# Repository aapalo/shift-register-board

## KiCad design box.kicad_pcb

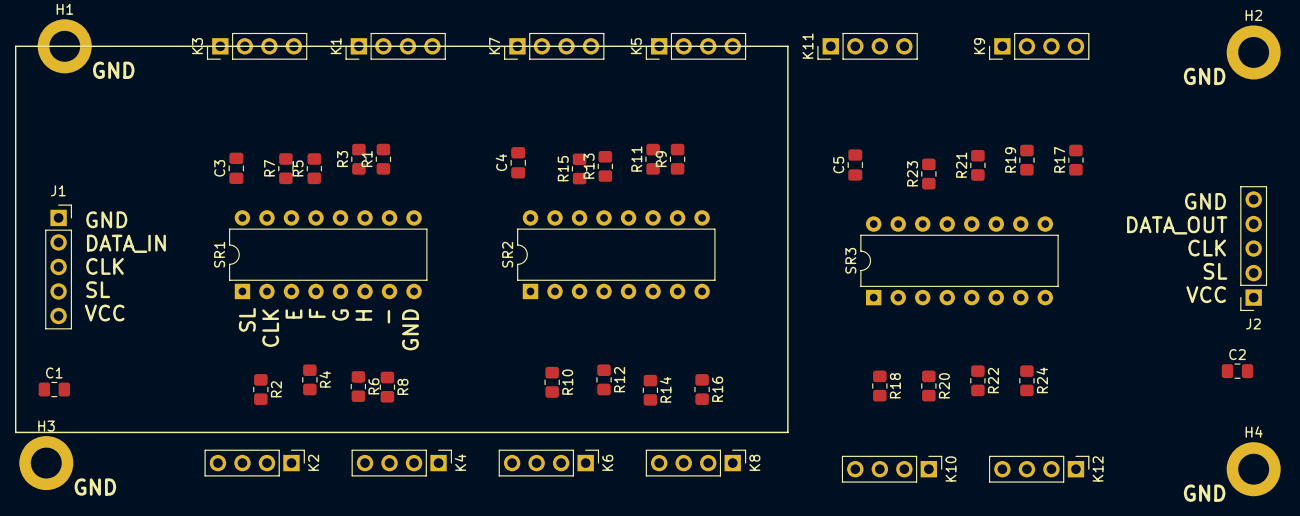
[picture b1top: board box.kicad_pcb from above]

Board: 2 copper layers, 50 parts (0 on the bottom side), 32 nets, no tracks yet.

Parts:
C1, C2, C3, C4, C5: 470n; C_0805_2012Metric_Pad1.18x1.45mm_HandSolder
H1, H2, H3, H4: MountingHole_Pad; MountingHole_3.2mm_M3_DIN965_Pad
J1, J2: Conn_01x05; PinSocket_1x05_P2.54mm_Vertical
K1, K2, K3, K4, K5, K6, K7, K8, K9, K10, K11, K12: Conn_01x04; PinHeader_1x04_P2.54mm_Vertical
R1, R2, R3, R4, R5, R6, R7, R8, R9, R10, R11, R12, R13, R14, R15, R16, R17, R18, R19, R20, R21, R22, R23, R24: 10k; R_0805_2012Metric_Pad1.20x1.40mm_HandSolder
SR1, SR2, SR3: Conn_02x08_Counter_Clockwise; DIP-16_W7.62mm

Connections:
/SR_CLK: J1.3, J2.3, SR1.2, SR2.2, SR3.2
/SR_DATA_2: SR1.10, SR2.9
/SR_DATA_3: SR2.10, SR3.9
/SR_QH: J2.4, SR1.9
/SR_SER2: J1.2, SR3.10
/SR_SL: J1.4, J2.2, SR1.1, SR2.1, SR3.1
/SR_VCC: C1.1, C2.1, C3.1, C4.1, C5.1, J1.5, J2.1, R1.2, R2.2, R3.2, R4.2, R5.2, R6.2, R7.2, R8.2, R9.2, R10.2, R11.2, R12.2, R13.2, R14.2, R15.2, R16.2, R17.2, R18.2, R19.2, R20.2, R21.2, R22.2, R23.2, R24.2, SR1.16, SR2.16, SR3.16
/Shift register 2/A: K5.4, R9.1, SR2.11
/Shift register 2/B: K5.2, R11.1, SR2.12
/Shift register 2/C: K7.4, R13.1, SR2.13
/Shift register 2/D: K7.2, R15.1, SR2.14
/Shift register 2/E: K6.4, R10.1, SR2.3
/Shift register 2/F: K6.2, R12.1, SR2.4
/Shift register 2/G: K8.4, R14.1, SR2.5
/Shift register 2/H: K8.2, R16.1, SR2.6
/Shift register 3/A: K9.4, R17.1, SR3.11
/Shift register 3/B: K9.2, R19.1, SR3.12
/Shift register 3/C: K11.4, R21.1, SR3.13
/Shift register 3/D: K11.2, R23.1, SR3.14
/Shift register 3/E: K10.4, R18.1, SR3.3
/Shift register 3/F: K10.2, R20.1, SR3.4
/Shift register 3/G: K12.4, R22.1, SR3.5
/Shift register 3/H: K12.2, R24.1, SR3.6
/Shift register/A: K1.4, R1.1, SR1.11
/Shift register/B: K1.2, R3.1, SR1.12
/Shift register/C: K3.4, R5.1, SR1.13
/Shift register/D: K3.2, R7.1, SR1.14
/Shift register/E: K2.4, R2.1, SR1.3
/Shift register/F: K2.2, R4.1, SR1.4
/Shift register/G: K4.4, R6.1, SR1.5
/Shift register/H: K4.2, R8.1, SR1.6
GND: C1.2, C2.2, C3.2, C4.2, C5.2, H1.1, H2.1, H3.1, H4.1, J1.1, J2.5, K1.1, K1.3, K2.1, K2.3, K3.1, K3.3, K4.1, K4.3, K5.1, K5.3, K6.1, K6.3, K7.1, K7.3, K8.1, K8.3, K9.1, K9.3, K10.1, K10.3, K11.1, K11.3, K12.1, K12.3, SR1.8, SR1.15, SR2.8, SR2.15, SR3.8, SR3.15

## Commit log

2021-09-20 Initial commit. Components placed. No traces yet.
